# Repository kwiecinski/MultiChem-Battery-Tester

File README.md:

# MultiChem-Battery-Tester
Multi-chemistry (Lithum, PB and others) battery charger/discharger with capacitance measurement and discharge graph for diffrent charge/load currents.

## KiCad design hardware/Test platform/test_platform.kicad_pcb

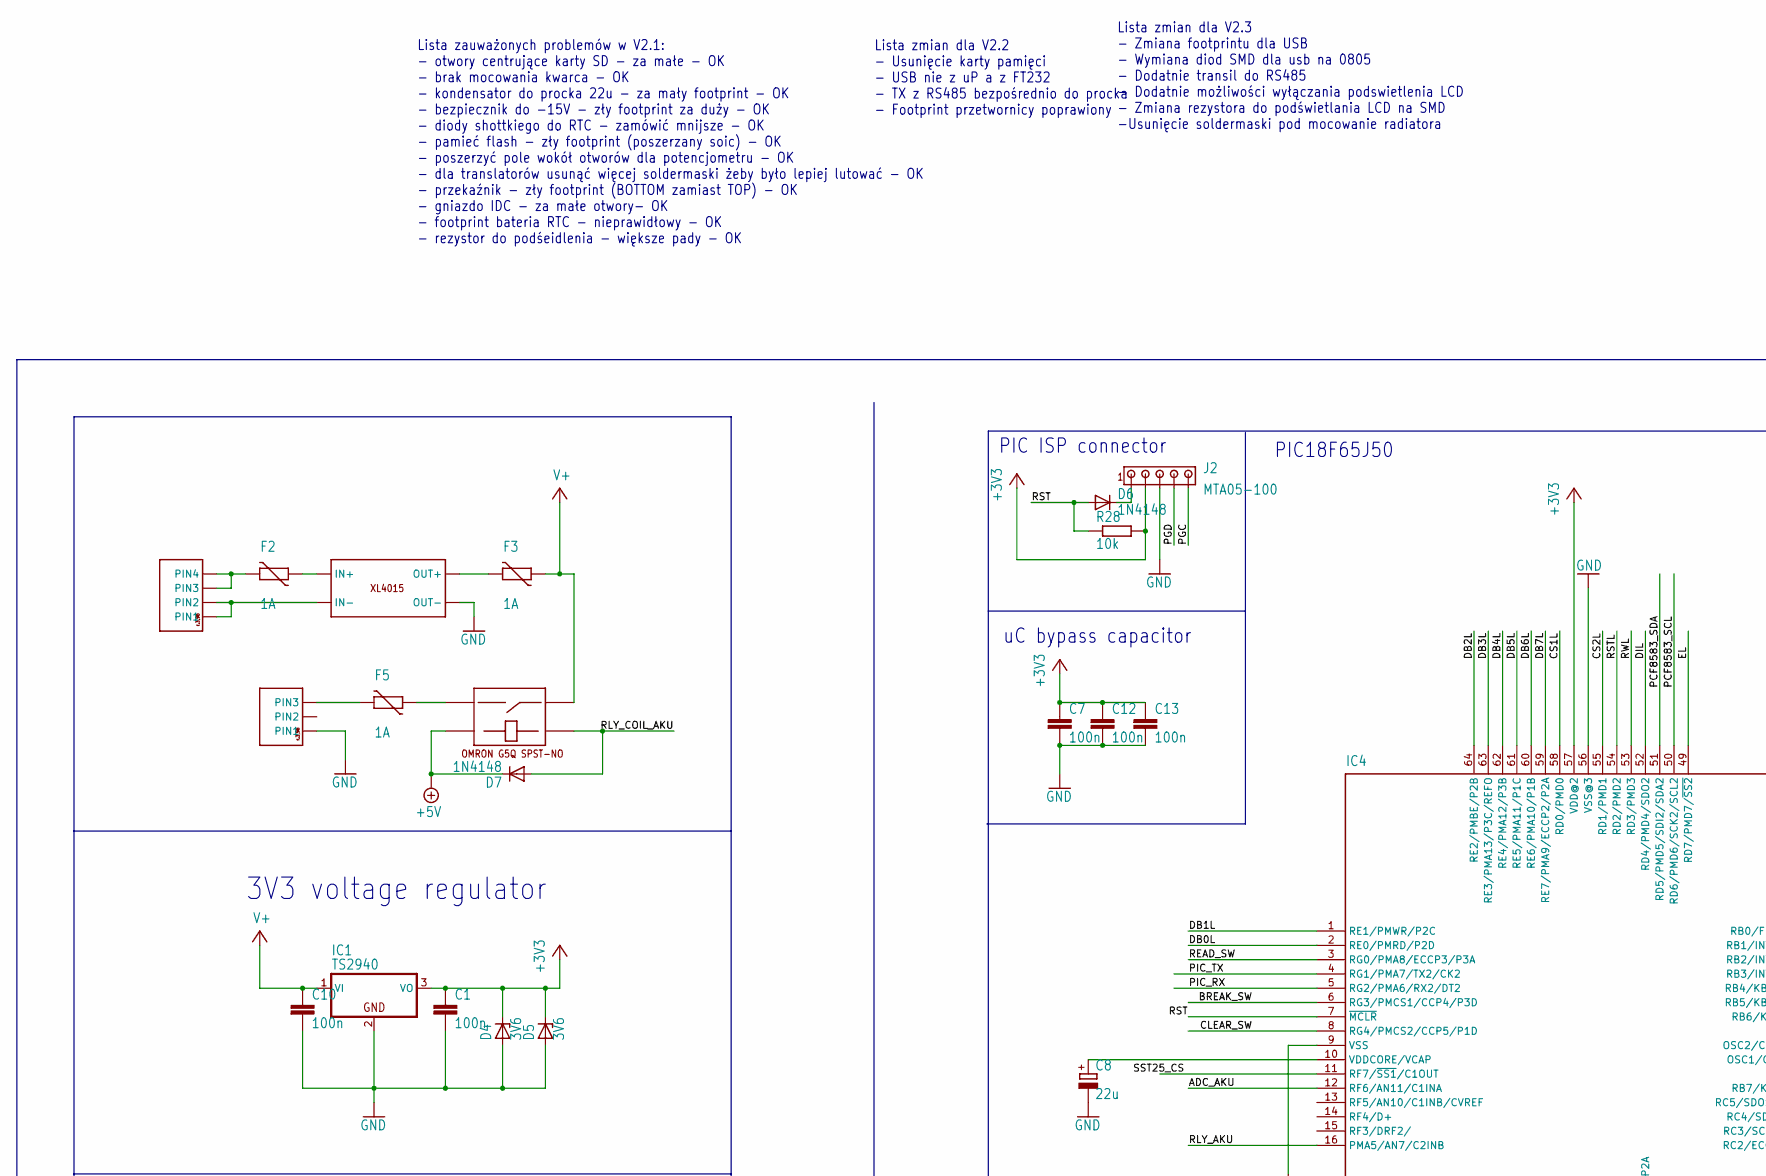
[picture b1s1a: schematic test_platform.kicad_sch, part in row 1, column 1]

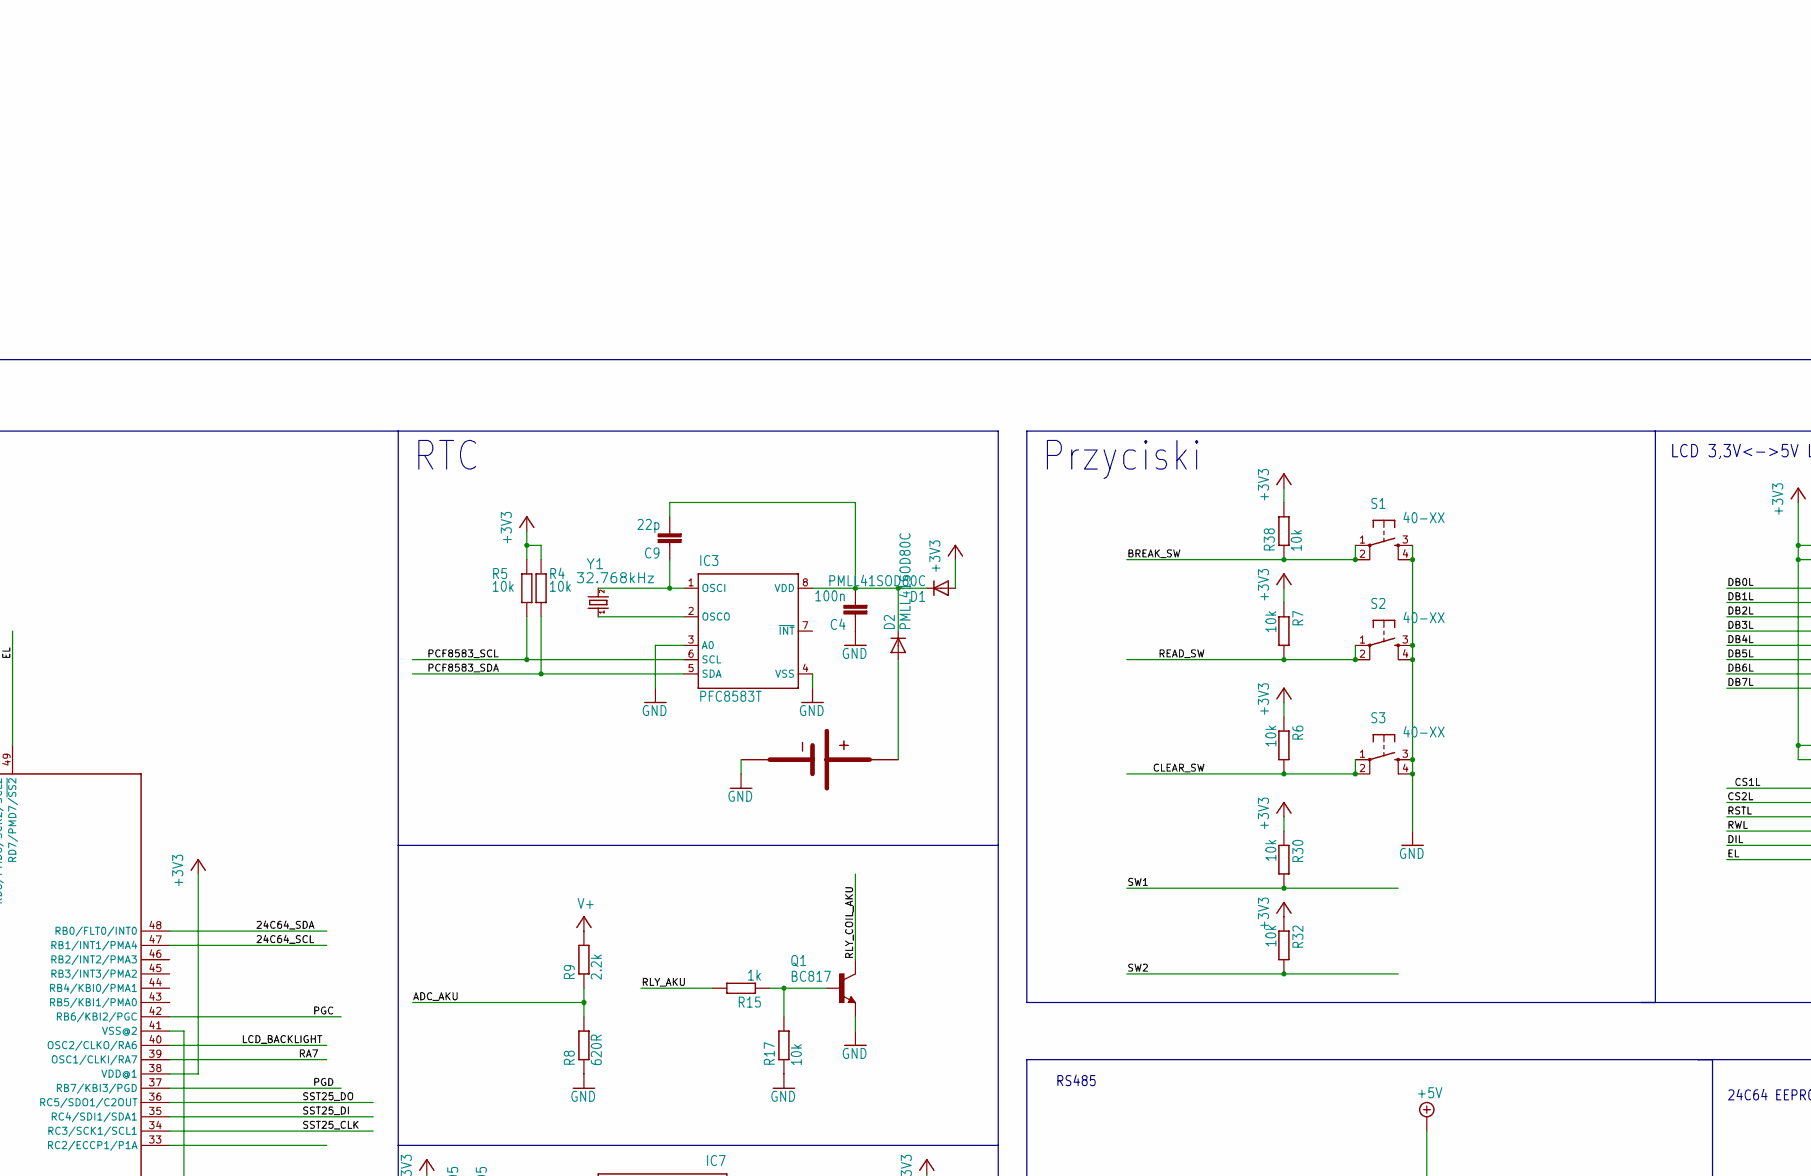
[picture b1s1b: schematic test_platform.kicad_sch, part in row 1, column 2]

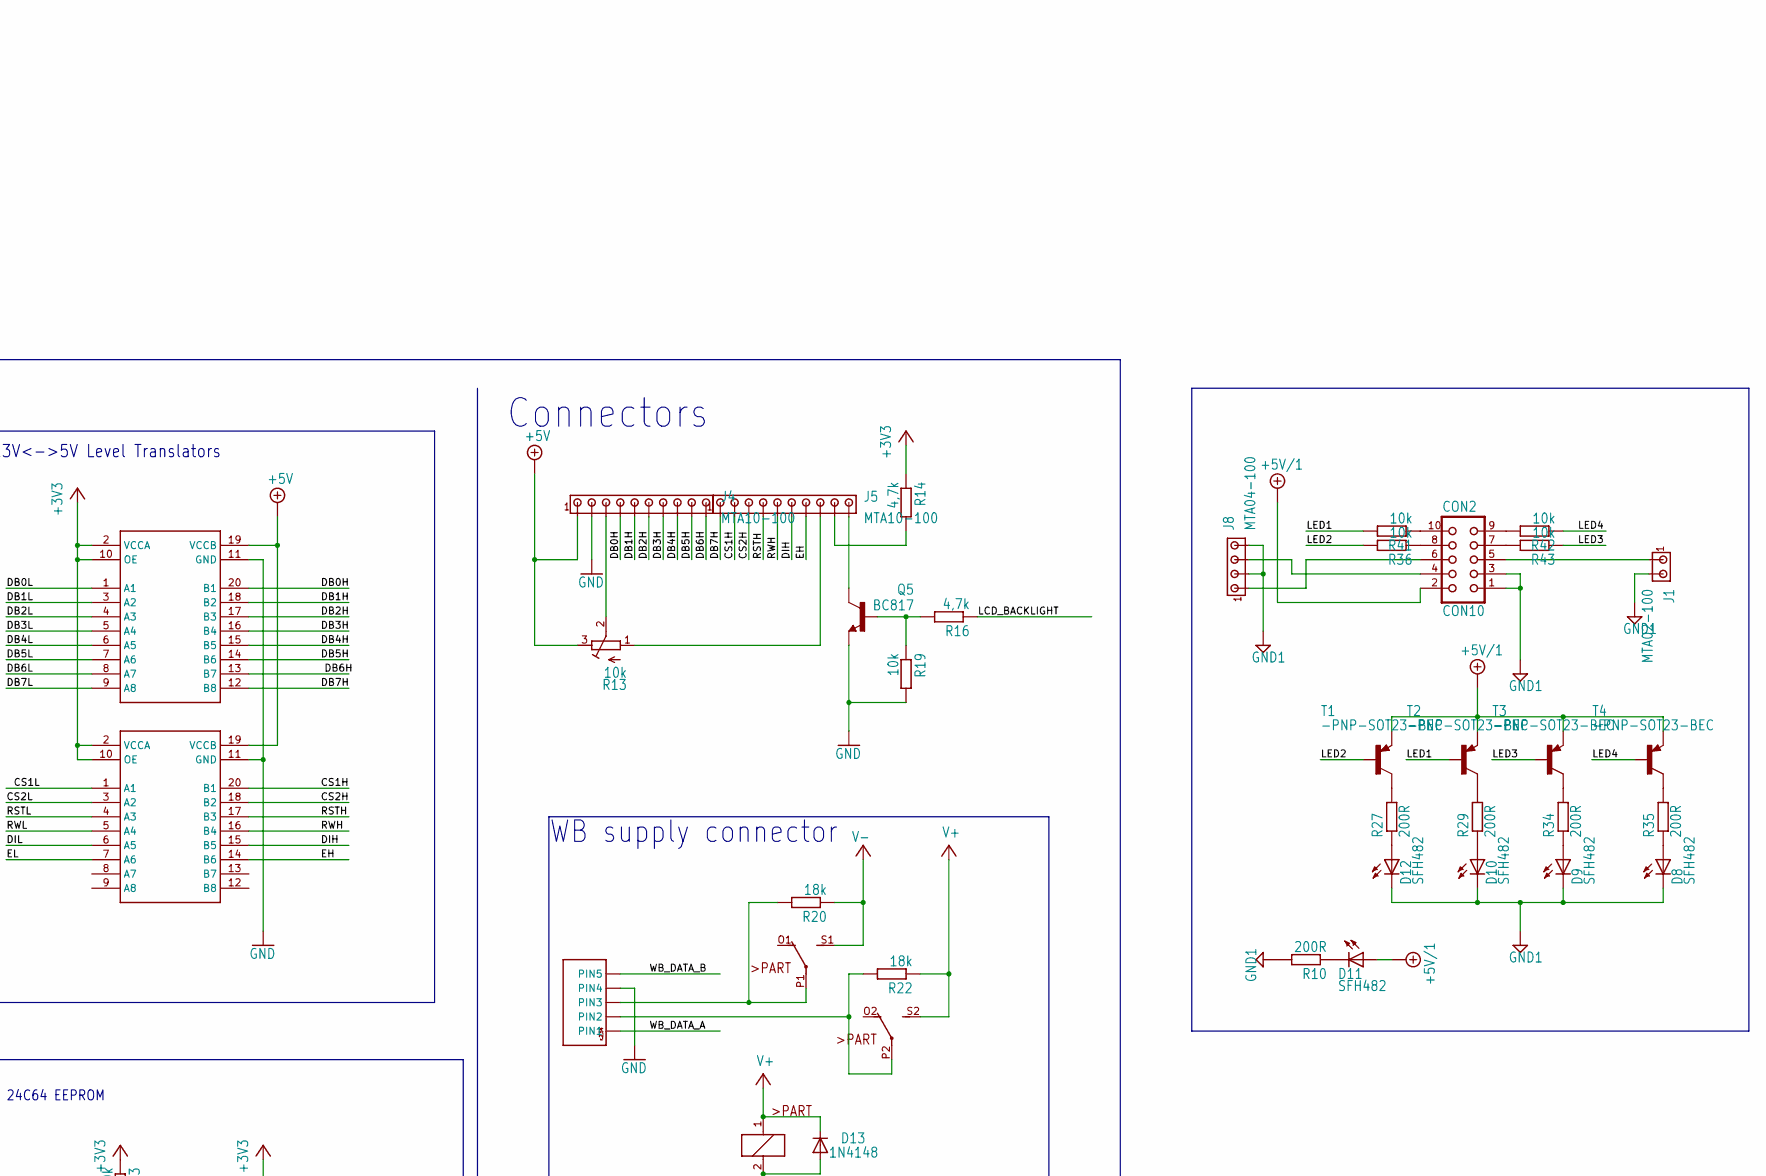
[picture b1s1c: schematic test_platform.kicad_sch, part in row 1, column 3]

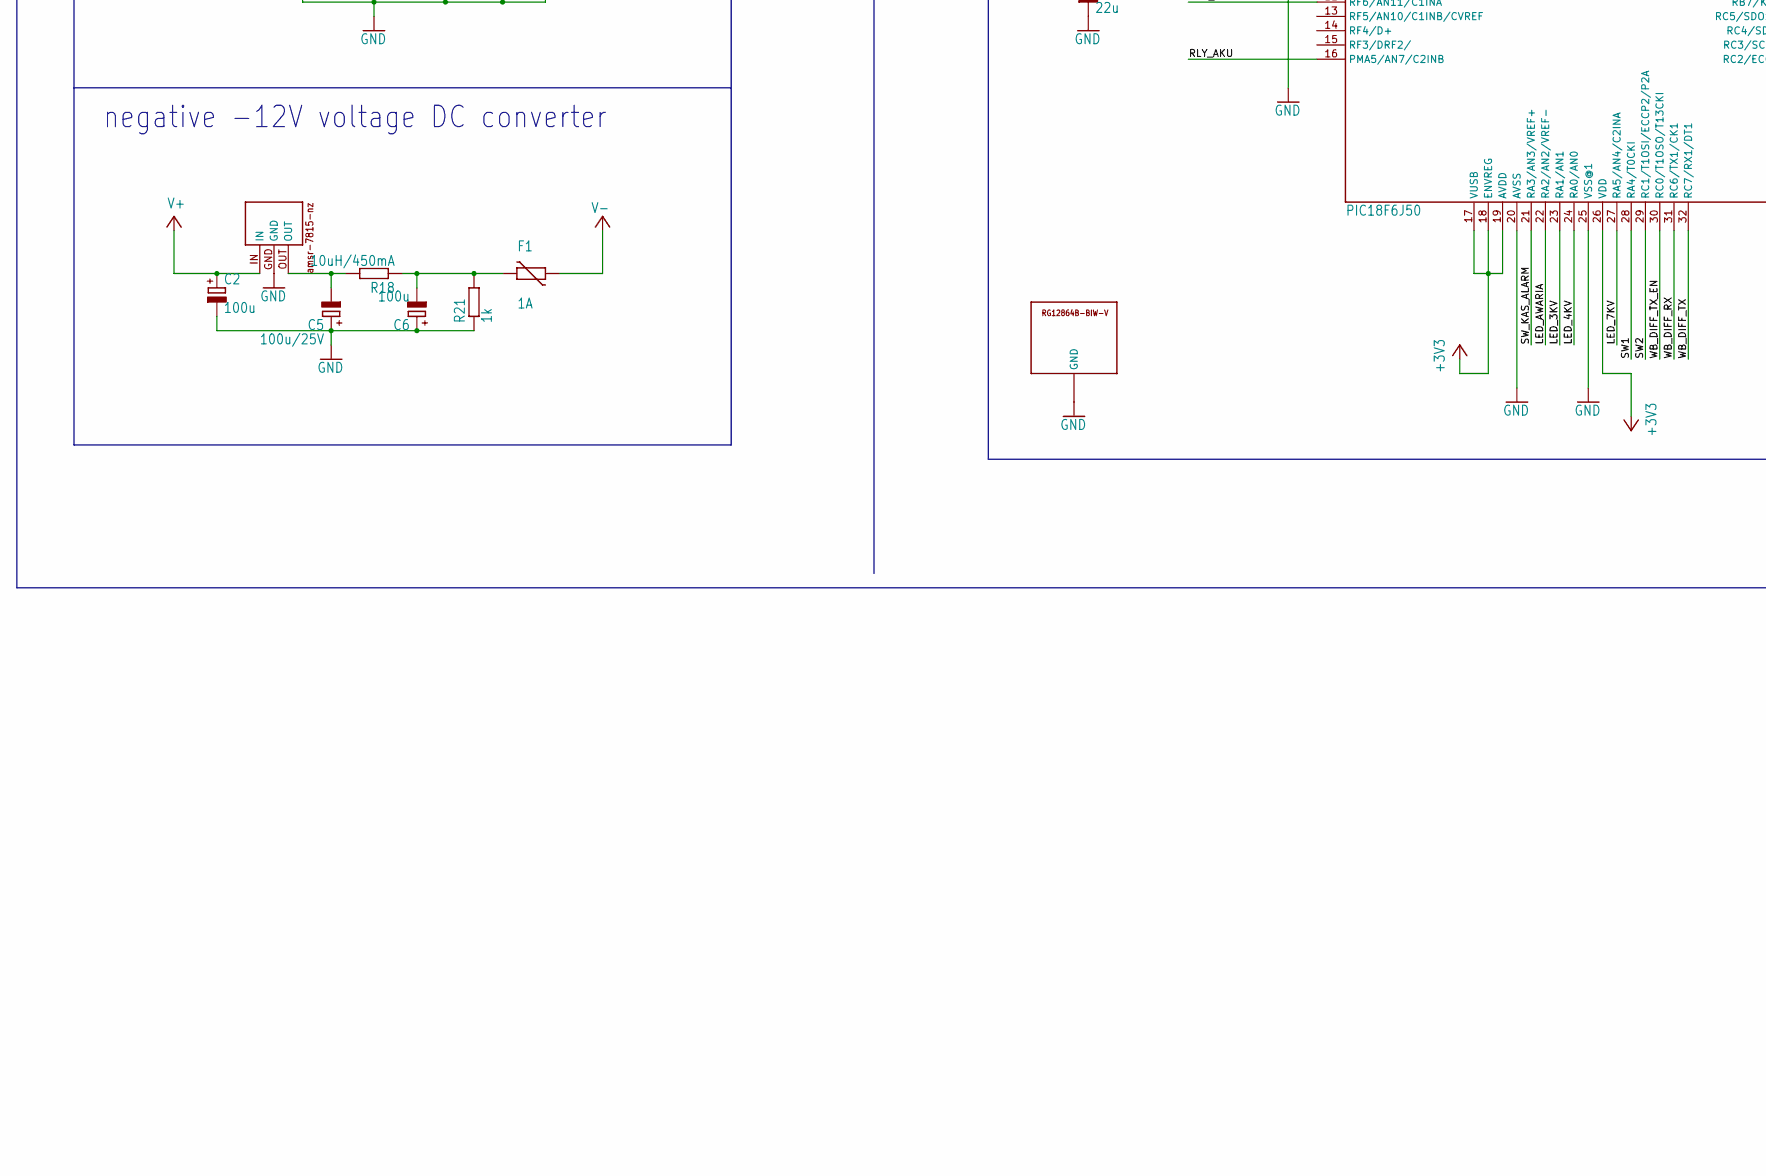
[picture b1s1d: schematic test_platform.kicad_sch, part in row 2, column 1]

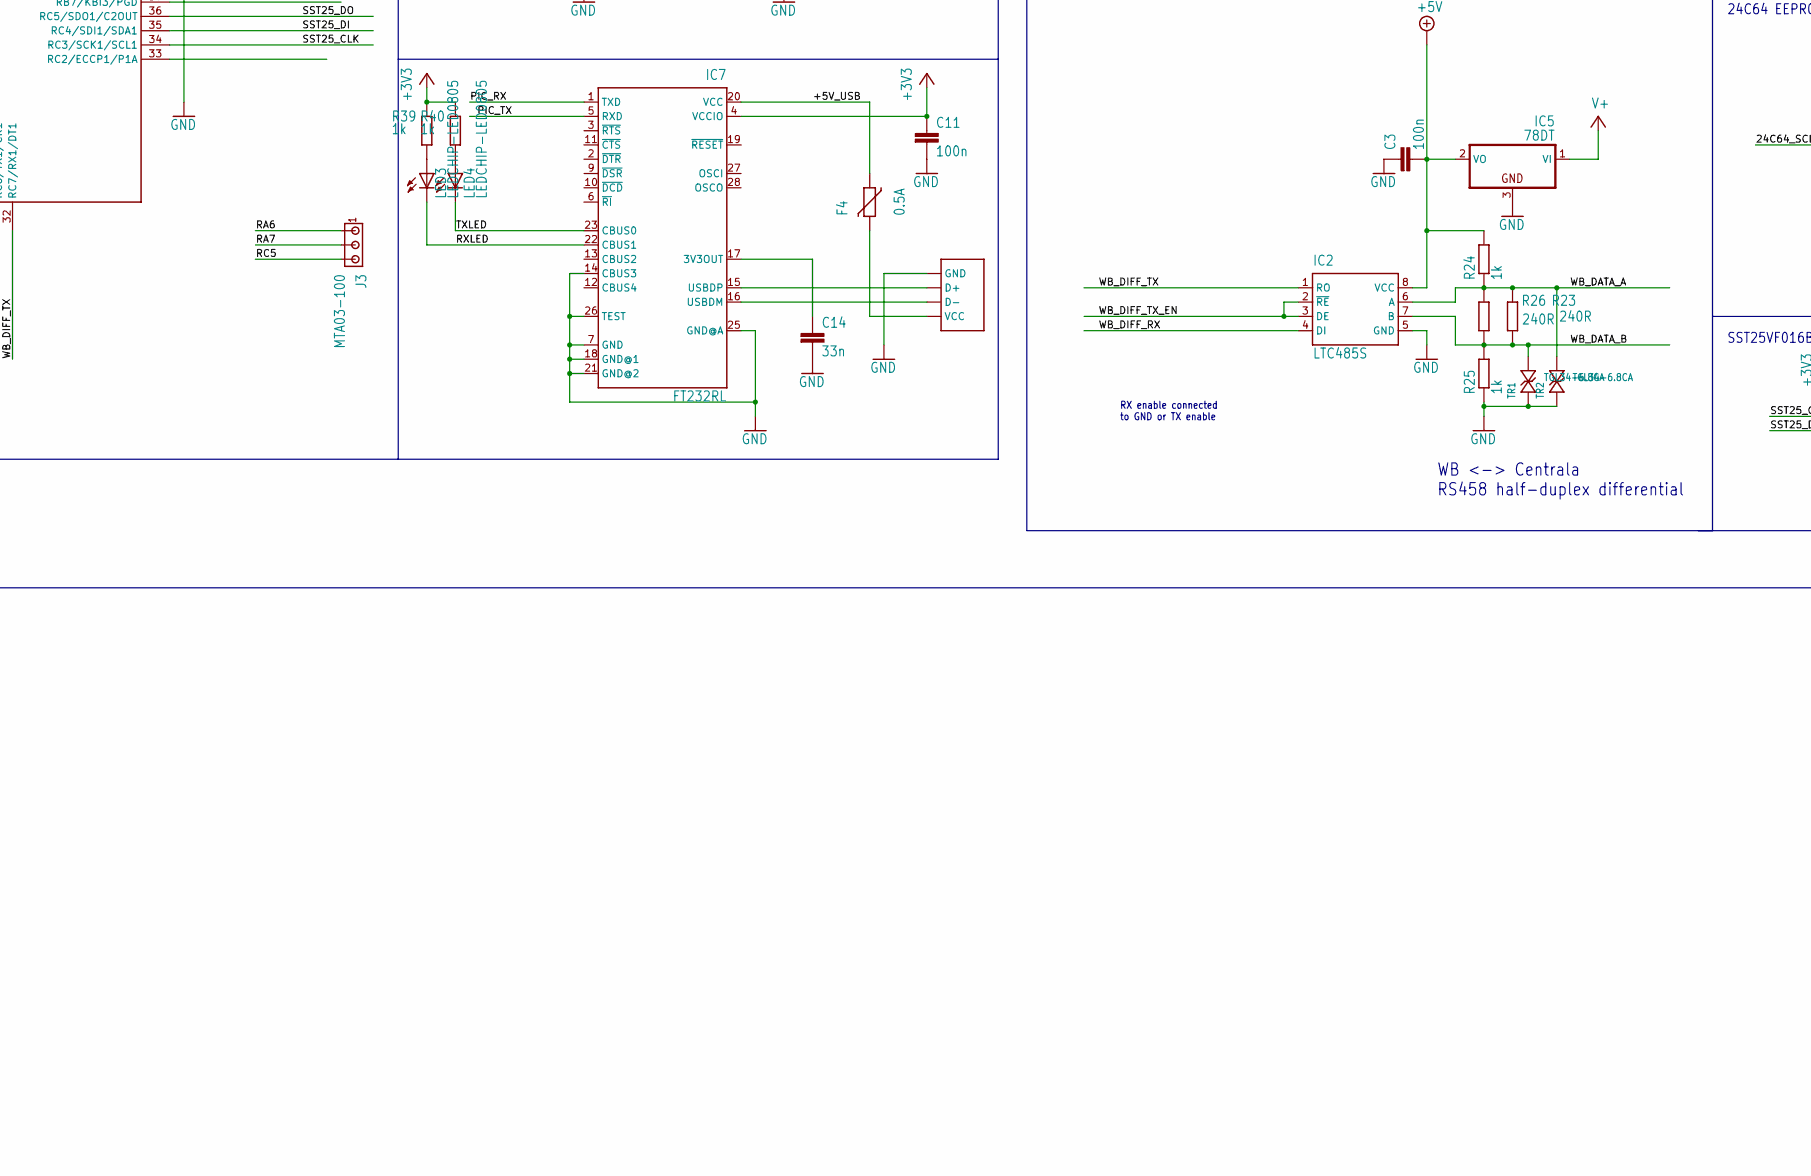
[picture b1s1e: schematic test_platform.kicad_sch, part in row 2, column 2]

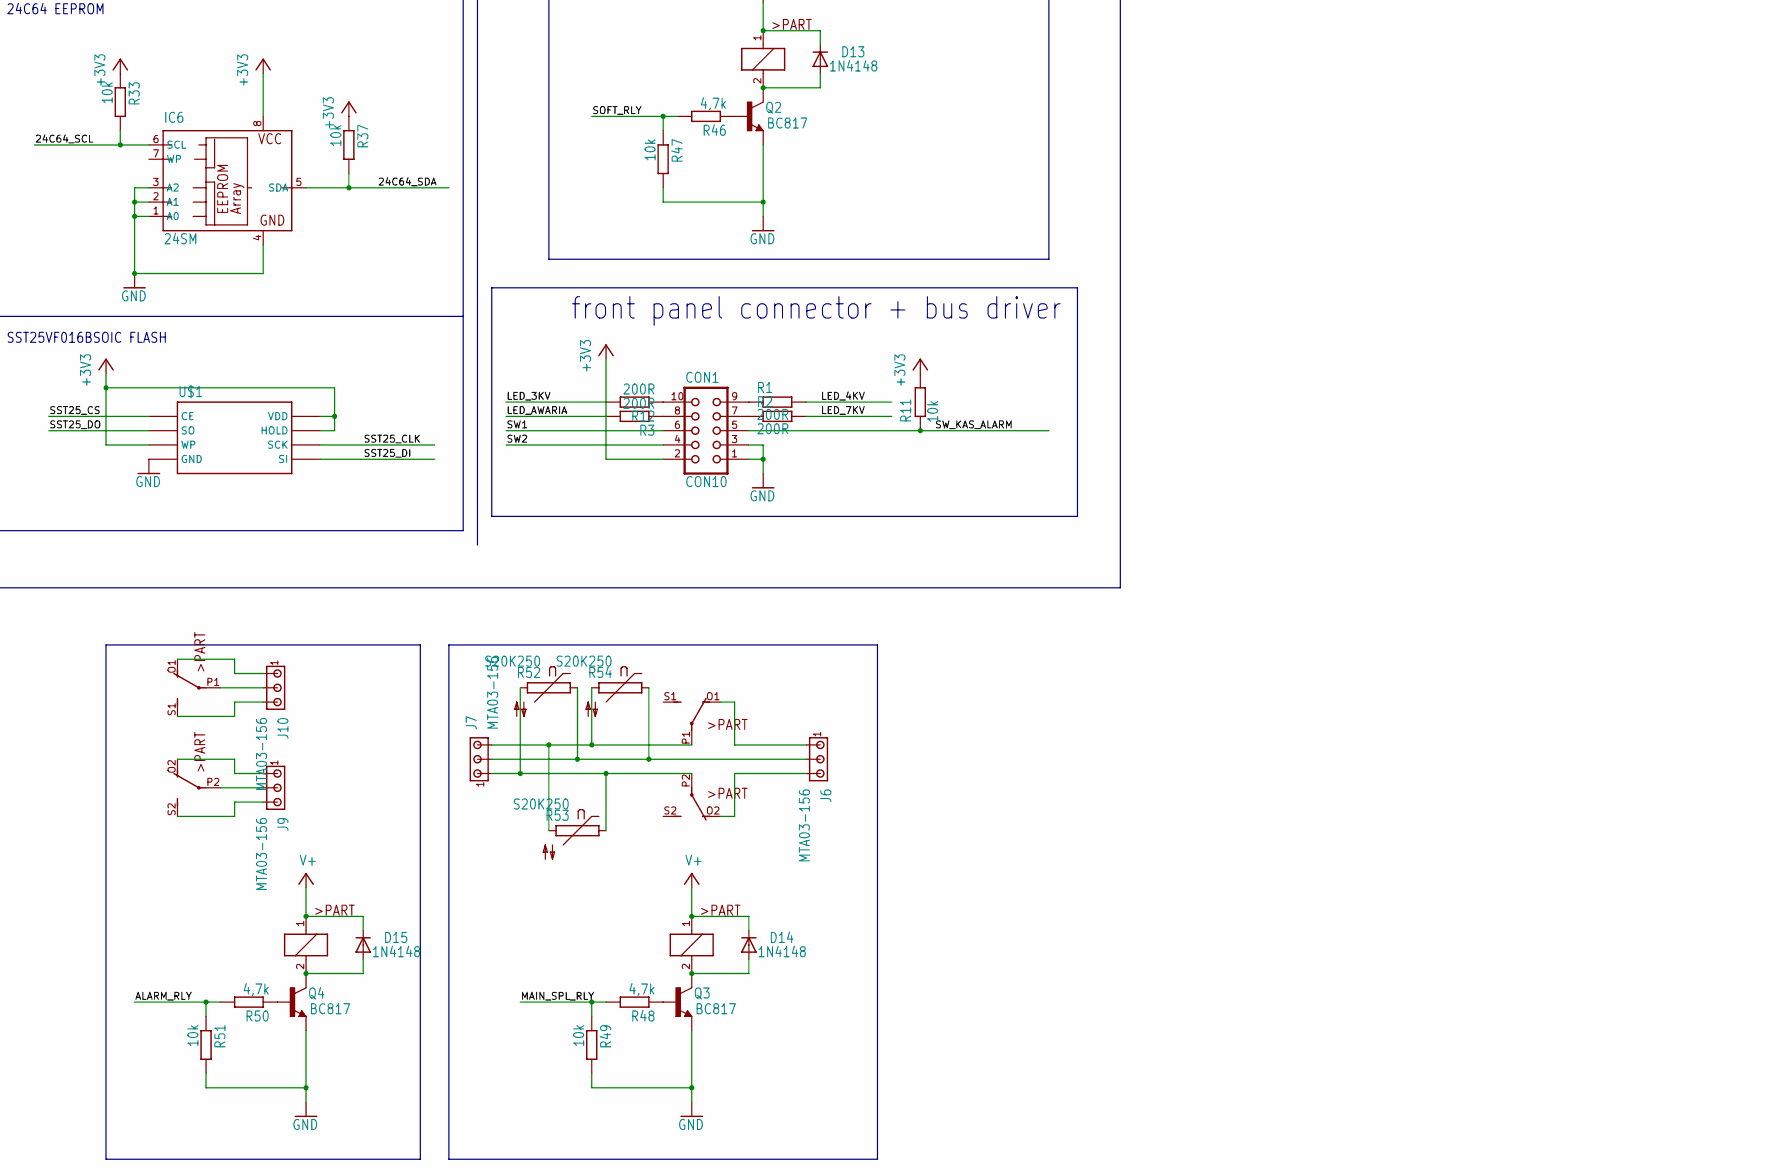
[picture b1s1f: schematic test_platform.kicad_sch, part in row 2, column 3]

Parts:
C1, C3, C4, C7, C10, C11, C12, C13: 100n; C0805
C2, C6: 100u; E2,5-7
C5: 100u/25V; E2,5-7
C8: 22u; SMC_D
C9: 22p; C0805
C14: 33n; C0805
CON1, CON2: CON10
D1, D2: PMLL41SOD80C; SOD80C
D4, D5: 3V6; SOD80C
D6, D7, D13, D14, D15: 1N4148; SOD80C
D8, D9, D10, D11, D12: SFH482
F1, F2, F3, F5: 1A; CT_CN1812
F4: 0.5A; CT_CN1812
IC1: TS2940; TO220V
IC2: LTC485S; SOIC8
IC3: PFC8583T; SO8-7_5
IC4: PIC18F6J50; TQFP64-10X10
IC5: 78DT; TO252
IC6: 24SM; SO-08M
IC7: FT232RL; SSOP28
J1: MTA02-100; 10X02MTA
J2: MTA05-100; 10X05MTA
J3: MTA03-100; 10X03MTA
J4, J5: MTA10-100; 10X10MTA
J6, J7, J9, J10: MTA03-156; 1X3MTA
J8: MTA04-100; 10X04MTA
K1: FTR-F1CA012V; G2R2
K2, K3: G2R2
LED3, LED4: LEDCHIP-LED0805; CHIP-LED0805
Q1, Q2, Q3, Q4, Q5: BC817; SOT23-BEC
R1, R2, R3, R10, R12, R27, R29, R34, R35: 200R; R0805
R4, R5, R6, R7, R11, R17, R19, R28, R30, R32, R33, R36, R37, R38, R41, R42, R43, R47, R49, R51: 10k; R0805
R8: 620R; R0805
R9: 2.2k; R0805
R13: 10k; RTRIM3299W
R14, R16, R46, R48, R50: 4,7k; R0805
R15, R21, R24, R25, R39, R40: 1k; R0805
R18: 10uH/450mA; M1206
R20, R22: 18k; R0805
R23, R26: 240R; R0805
R52, R53, R54: S20K250
S1, S2, S3: 40-XX; B3F_40XXA
T1, T2, T3, T4: -PNP-SOT23-BEC; SOT23-BEC
TR1, TR2: TGL34-6.8CA; DO214AC+MINIMELF_BIDIR
U$1: SST25VF016B; SOIC8(S2A)
U$2: AMSR-7815-NZ; AIMTEC_DC
U$3: USBB; USB_B
U$4, U$5: TXB010X; TSSOP20
U$6: G5Q; G5Q_SPSTNO
U$7: XL4015; DC_BUCK
U$8: 4PIN_R3,96
U$9: 3PIN_R3,96
U$10: 5PIN_R2,54
U$11: CR2032
U$12: RG12864B-BIW-V
Y1: 32.768kHz; CRYSTAL-PTH-2X6-CYL-KIT

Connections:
24C64_SCL: IC4.47 (RB1/INT1/PMA4), IC6.6 (SCL), R33.2
24C64_SDA: IC4.48 (RB0/FLT0/INT0), IC6.5 (SDA), R37.2
+3V3: C1.1, C7.1, C11.1, C12.1, C13.1, CON1.2, D1.A, D4.C, D5.C, IC1.3 (VO), IC4.17 (VUSB), IC4.18 (ENVREG), IC4.19 (AVDD), IC4.26 (VDD), IC4.38 (VDD@1), IC4.57 (VDD@2), IC6.8 (VCC), IC7.4 (VCCIO), J2.2, R4.1, R5.1, R6.1, R7.1, R11.2, R14.1, R28.2, R30.1, R32.1, R33.1, R37.1, R38.2, R39.1, R40.1, U$1.3 (WP), U$1.7 (HOLD), U$1.8 (VDD), U$4.2 (VCCA), U$4.10 (OE), U$5.2 (VCCA), U$5.10 (OE)
+5V: C3.2, D7.C, IC2.8 (VCC), IC5.2 (VO), J4.1, R13.3 (E), R24.2, U$4.19 (VCCB), U$5.19 (VCCB), U$6.C2
+5V/1: CON2.2, D11.A, T1.E, T2.E, T3.E, T4.E
+5V_USB: F4.1, IC7.20 (VCC)
ADC_AKU: IC4.12 (RF6/AN11/C1INA), R8.2, R9.1
BREAK_SW: IC4.6 (RG3/PMCS1/CCP4/P3D), R38.1, S1.1, S1.2 (P1)
CLEAR_SW: IC4.8 (RG4/PMCS2/CCP5/P1D), R6.2, S3.1, S3.2 (P1)
CS1H: J5.2, U$5.20 (B1)
CS1L: IC4.58 (RD0/PMD0), U$5.1 (A1)
CS2H: J5.3, U$5.18 (B2)
CS2L: IC4.55 (RD1/PMD1), U$5.3 (A2)
DB0H: J4.4, U$4.20 (B1)
DB0L: IC4.2 (RE0/PMRD/P2D), U$4.1 (A1)
DB1H: J4.5, U$4.18 (B2)
DB1L: IC4.1 (RE1/PMWR/P2C), U$4.3 (A2)
DB2H: J4.6, U$4.17 (B3)
DB2L: IC4.64 (RE2/PMBE/P2B), U$4.4 (A3)
DB3H: J4.7, U$4.16 (B4)
DB3L: IC4.63 (RE3/PMA13/P3C/REFO), U$4.5 (A4)
DB4H: J4.8, U$4.15 (B5)
DB4L: IC4.62 (RE4/PMA12/P3B), U$4.6 (A5)
DB5H: J4.9, U$4.14 (B6)
DB5L: IC4.61 (RE5/PMA11/P1C), U$4.7 (A6)
DB6H: J4.10, U$4.13 (B7)
DB6L: IC4.60 (RE6/PMA10/P1B), U$4.8 (A7)
DB7H: J5.1, U$4.12 (B8)
DB7L: IC4.59 (RE7/PMA9/ECCP2/P2A), U$4.9 (A8)
DIH: J5.6, U$5.15 (B5)
DIL: IC4.52 (RD4/PMD4/SDO2), U$5.6 (A5)
EH: J5.7, U$5.14 (B6)
EL: IC4.49 (RD7/PMD7/~SS2), U$5.7 (A6)
GND: C1.2, C2.-, C3.1, C4.1, C5.+, C6.+, C7.2, C8.-, C10.2, C11.2, C12.2, C13.2, C14.2, CON1.1, CON1.3, D4.A, D5.A, IC1.2 (GND), IC2.5 (GND), IC3.3 (A0), IC3.4 (VSS), IC4.9 (VSS), IC4.20 (AVSS), IC4.25 (VSS@1), IC4.41 (VSS@2), IC4.56 (VSS@3), IC5.3 (GND), IC6.1 (A0), IC6.2 (A1), IC6.3 (A2), IC6.4 (GND), IC7.7 (GND), IC7.14 (CBUS3), IC7.18 (GND@1), IC7.21 (GND@2), IC7.25 (GND@A), IC7.26 (TEST), J2.3, J4.2, Q1.E, Q2.E, Q3.E, Q4.E, Q5.E, R8.1, R17.1, R19.2, R21.1, R25.1, R47.2, R49.2, R51.2, S1.3 (S), S1.4 (S1), S2.3 (S), S2.4 (S1), S3.3 (S), S3.4 (S1), TR1.P$1, TR2.P$1, U$1.4 (GND), U$2.GND, U$3.GND1 (GND), U$3.GND2 (GND), U$3.GND3 (GND), U$3.GND4 (GND), U$3.GND5 (GND), U$3.GND6 (GND), U$4.11 (GND), U$5.11 (GND), U$7.OUT-, U$9.P$1 (PIN1), U$10.P$4 (PIN4), U$11.M, U$12.P$1, U$12.P$2, U$12.P$3, U$12.P$4
GND1: CON2.1, CON2.3, D8.K (C), D9.K (C), D10.K (C), D12.K (C), J1.2, J8.2, J8.4, R10.2
LCD_BACKLIGHT: IC4.40 (OSC2/CLKO/RA6), R16.1
LED1: R41.2, T2.B
LED2: R36.2, T1.B
LED3: R43.1, T3.B
LED4: R42.1, T4.B
LED_3KV: IC4.23 (RA1/AN1), R12.2
LED_4KV: IC4.24 (RA0/AN0), R1.2
LED_7KV: IC4.27 (RA5/AN4/C2INA), R2.2
LED_AWARIA: IC4.22 (RA2/AN2/VREF-), R3.2
unnamed: CON1.9, R1.1
unnamed: C5.-, R18.2, U$2.OUT
unnamed: CON1.7, R2.1
unnamed: IC3.2 (OSCO), Y1.1
unnamed: CON1.8, R3.1
unnamed: CON1.10, R12.1
unnamed: D6.C, J2.1
unnamed: D2.A, U$11.P
unnamed: C9.1, IC3.1 (OSCI), Y1.2
unnamed: C4.2, C9.2, D1.C, D2.C, IC3.8 (VDD)
unnamed: J5.9, R14.2
unnamed: C8.+, IC4.10 (VDDCORE/VCAP)
unnamed: J4.3, R13.2 (S)
unnamed: IC7.15 (USBDP), U$3.D+
unnamed: Q1.B, R15.1, R17.2
unnamed: F2.2, U$8.P$3 (PIN3), U$8.P$4 (PIN4)
unnamed: U$7.IN-, U$8.P$1 (PIN1), U$8.P$2 (PIN2)
unnamed: F2.1, U$7.IN+
unnamed: F3.2, U$7.OUT+
unnamed: IC7.16 (USBDM), U$3.D-
unnamed: F5.2, U$9.P$3 (PIN3)
unnamed: J5.10, Q5.C
unnamed: Q5.B, R16.2, R19.1
unnamed: F5.1, U$6.S2
unnamed: LED3.A, R39.2
unnamed: C14.1, IC7.17 (3V3OUT)
unnamed: F4.2, U$3.VCC
unnamed: LED4.A, R40.2
unnamed: D11.K (C), R10.1
unnamed: CON2.4, J8.3
unnamed: R27.2, T1.C
unnamed: D12.A, R27.1
unnamed: D9.A, R34.1
unnamed: J5.8, R13.1 (A)
unnamed: R34.2, T3.C
unnamed: CON2.5, J1.1
unnamed: C6.-, F1.2, R18.1, R21.2
unnamed: CON2.6, J8.1
unnamed: R29.2, T2.C
unnamed: D10.A, R29.1
unnamed: D8.A, R35.1
unnamed: R35.2, T4.C
unnamed: K1.P2, R22.2, U$10.P$2 (PIN2)
unnamed: K1.P1, R20.2, U$10.P$3 (PIN3)
unnamed: D13.A, K1.2, Q2.C
unnamed: Q2.B, R46.1
unnamed: CON2.8, R36.1
unnamed: CON2.10, R41.1
unnamed: CON2.9, R42.2
unnamed: CON2.7, R43.2
unnamed: J6.2, J7.2, R52.1, R54.1
unnamed: J7.3, K2.P1, R53.2, R54.2
unnamed: J6.1, K2.O1 (O)
unnamed: J7.1, K2.P2, R52.2, R53.1
unnamed: J6.3, K2.O2 (O)
unnamed: D14.A, K2.2, Q3.C
unnamed: Q3.B, R48.1
unnamed: D15.A, K3.2, Q4.C
unnamed: Q4.B, R50.1
unnamed: J10.2, K3.P1
unnamed: J10.1, K3.O1 (O)
unnamed: J10.3, K3.S1 (S)
unnamed: J9.1, K3.O2 (O)
unnamed: J9.2, K3.P2
unnamed: J9.3, K3.S2 (S)
PCF8583_SCL: IC3.6 (SCL), IC4.50 (RD6/PMD6/SCK2/SCL2), R5.2
PCF8583_SDA: IC3.5 (SDA), IC4.51 (RD5/PMD5/SDI2/SDA2), R4.2
PGC: IC4.42 (RB6/KBI2/PGC), J2.5
PGD: IC4.37 (RB7/KBI3/PGD), J2.4
PIC_RX: IC4.5 (RG2/PMA6/RX2/DT2), IC7.1 (TXD)
PIC_TX: IC4.4 (RG1/PMA7/TX2/CK2), IC7.5 (RXD)
RA6: J3.1
RA7: IC4.39 (OSC1/CLKI/RA7), J3.2
READ_SW: IC4.3 (RG0/PMA8/ECCP3/P3A), R7.2, S2.1, S2.2 (P1)
RLY_AKU: IC4.16 (PMA5/AN7/C2INB), R15.2
RLY_COIL_AKU: D7.A, Q1.C, U$6.C1
RST: D6.A, IC4.7 (~MCLR), R28.1
RSTH: J5.4, U$5.17 (B3)
RSTL: IC4.54 (RD2/PMD2), U$5.4 (A3)
RWH: J5.5, U$5.16 (B4)
RWL: IC4.53 (RD3/PMD3), U$5.5 (A4)
RXLED: IC7.22 (CBUS1), LED3.C
SOFT_RLY: IC4.33 (RC2/ECCP1/P1A), R46.2, R47.1
SW1: CON1.6, IC4.28 (RA4/T0CKI), R30.2
SW2: CON1.4, IC4.29 (RC1/T1OSI/ECCP2/P2A), R32.2
SW_KAS_ALARM: CON1.5, IC4.21 (RA3/AN3/VREF+), R11.1
TXLED: IC7.23 (CBUS0), LED4.C
V+: C2.+, C10.1, D13.C, D14.C, D15.C, F3.1, IC1.1 (VI), IC5.1 (VI), K1.1, K1.S2 (S), K2.1, K3.1, R9.2, R22.1, U$2.IN, U$6.S1
V-: F1.1, K1.S1 (S), R20.1
WB_DATA_A: IC2.6 (A), R23.2, R24.1, R26.2, TR2.P$2, U$10.P$1 (PIN1)
WB_DATA_B: IC2.7 (B), R23.1, R25.2, R26.1, TR1.P$2, U$10.P$5 (PIN5)
WB_DIFF_RX: IC2.4 (DI), IC4.31 (RC6/TX1/CK1)
WB_DIFF_TX: IC2.1 (RO), IC4.32 (RC7/RX1/DT1)
WB_DIFF_TX_EN: IC2.2 (~RE), IC2.3 (DE), IC4.30 (RC0/T1OSO/T13CKI)

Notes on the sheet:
Lista zmian dla V2.3 - Zmiana footprintu dla USB - Wymiana diod SMD dla usb na 0805 - Dodatnie transil do RS485 - Dodatnie możliwości wyłączania podswietlenia LCD - Zmiana rezystora do podświetlania LCD na SMD -Usunięcie soldermaski pod mocowanie radiatora
24C64 EEPROM
uC bypass capacitor
Connectors
Lista zmian dla V2.2 - Usunięcie karty pamięci - USB nie z uP a z FT232 - TX z RS485 bezpośrednio do procka - Footprint przetwornicy poprawiony
front panel connector + bus driver
SST25VF016BSOIC FLASH
Przyciski
RS485
RTC
PIC18F65J50
RX enable connected to GND or TX enable
Lista zauważonych problemów w V2.1: - otwory centrujące karty SD - za małe - OK - brak mocowania kwarca - OK - kondensator do procka 22u - za mały footprint - OK - bezpiecznik do -15V - zły footprint za duży - OK - diody shottkiego do RTC - zamówić mnijsze - OK - pamieć flash - zły footprint (posze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
LCD 3,3V<->5V Level Translators
PIC ISP connector
WB <-> Centrala RS458 half-duplex differential
3V3 voltage regulator
WB supply connector
negative -12V voltage DC converter

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
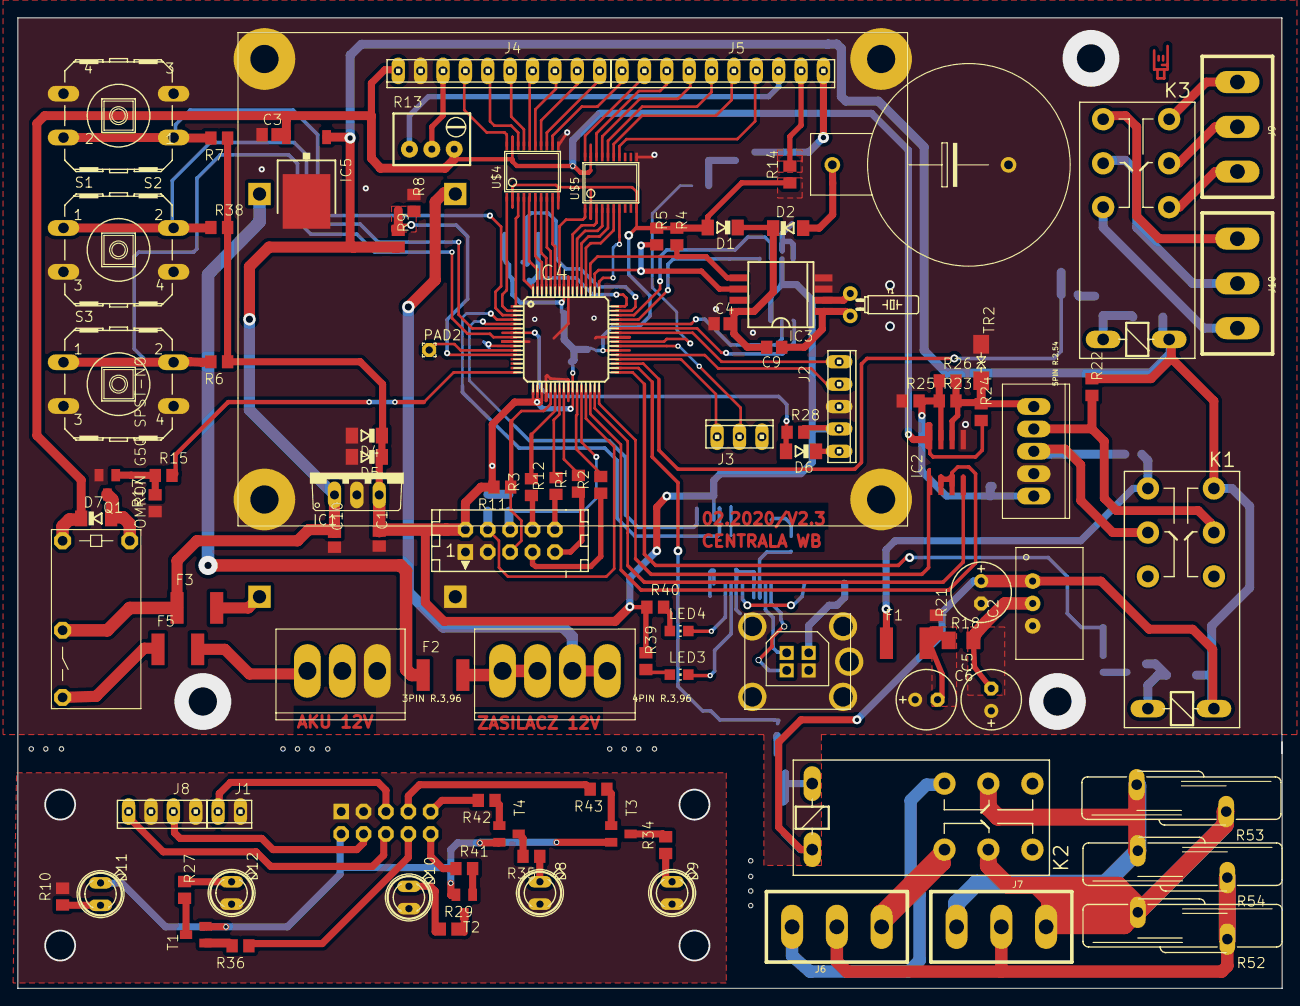
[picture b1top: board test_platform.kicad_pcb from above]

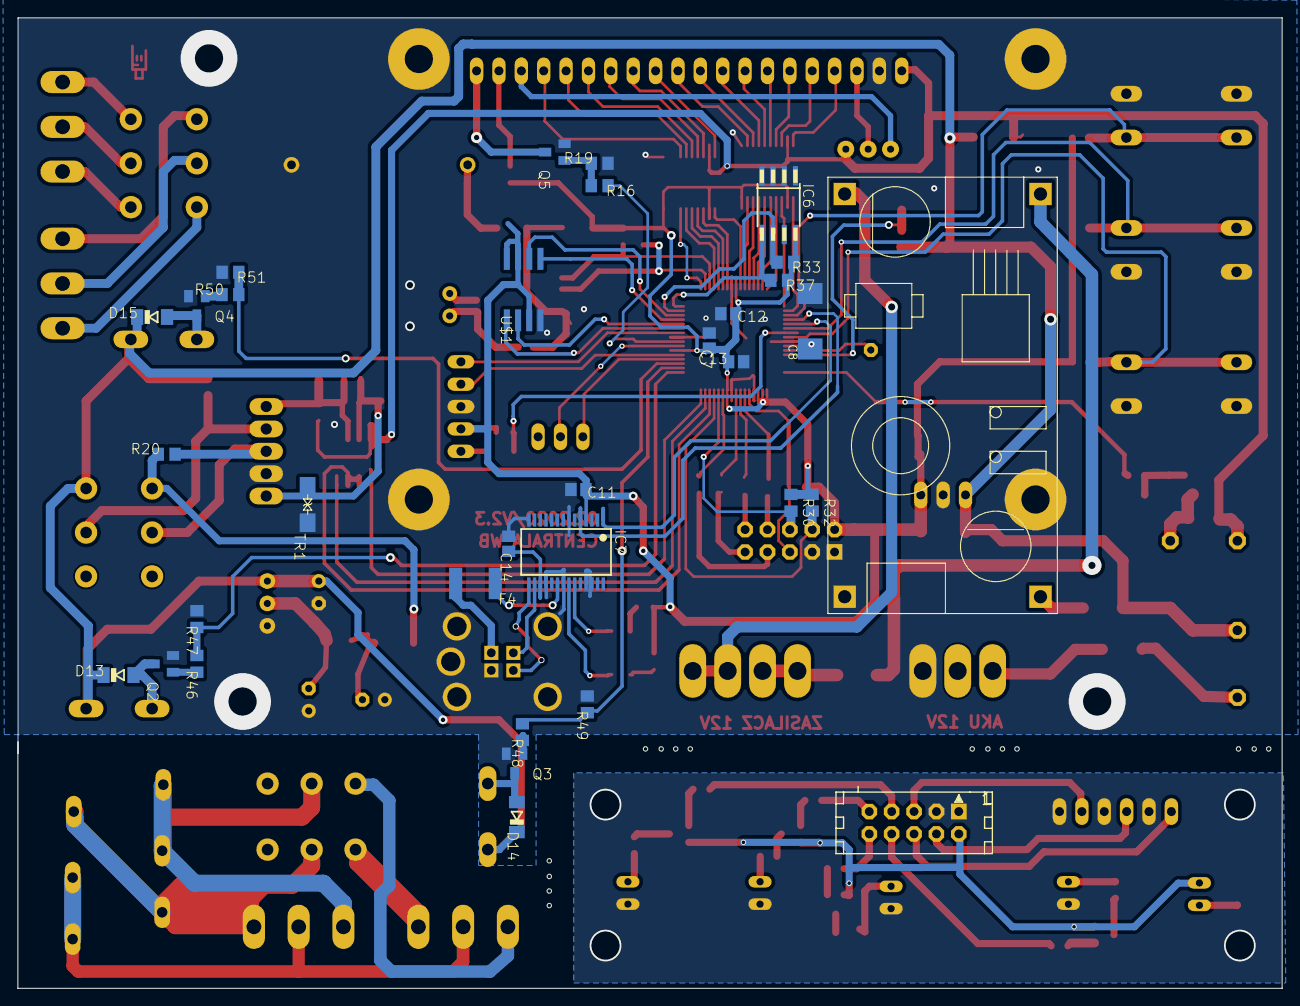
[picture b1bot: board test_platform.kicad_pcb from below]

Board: 2 copper layers, 143.5 x 110.2 mm, 151 parts (33 on the bottom side), 145 nets.

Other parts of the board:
@HOLE0, @HOLE1, @HOLE2, @HOLE3, @HOLE4, @HOLE5, @HOLE6, @HOLE7, @HOLE8, @HOLE9, @HOLE10, @HOLE11, @HOLE12, @HOLE13, @HOLE14: (no value)
PAD2: 1,6_0,8
